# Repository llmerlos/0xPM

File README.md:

# PICCTRL - 0xPM
## 3x6 + 4 Split Ortholinear Keyboard with on board MCU

## Characteristics:
* [FAK](https://github.com/semickolon/fak) powered
* CH552
* ESD, over-current, short-circuit, reverse polarity protection.
* [Acrylic case](https://github.com/llmerlos/OxPM/PCB/svgs).
* Reversible PCB
* MX and Choc V1 compatibility.

### Choc V1

### MX

### Keymap
Nickel files available [here](https://github.com/llmerlos/OxPM/firmware/).

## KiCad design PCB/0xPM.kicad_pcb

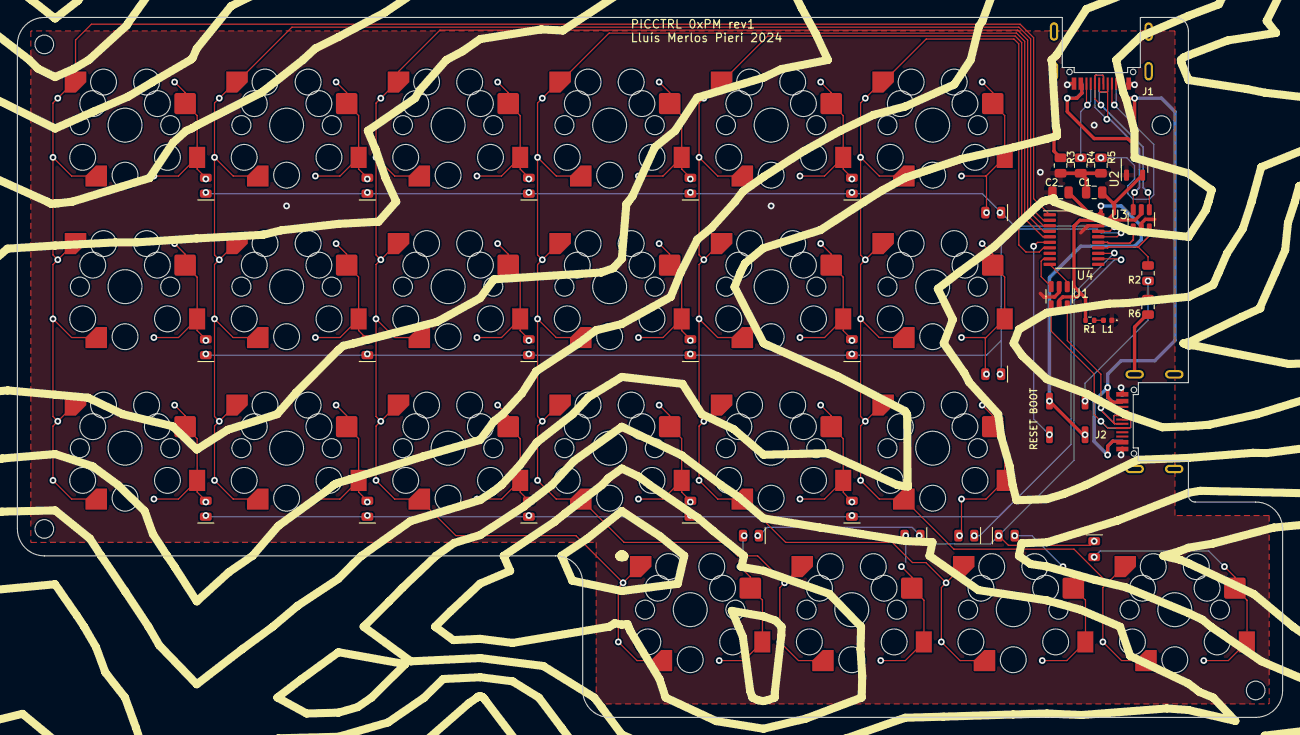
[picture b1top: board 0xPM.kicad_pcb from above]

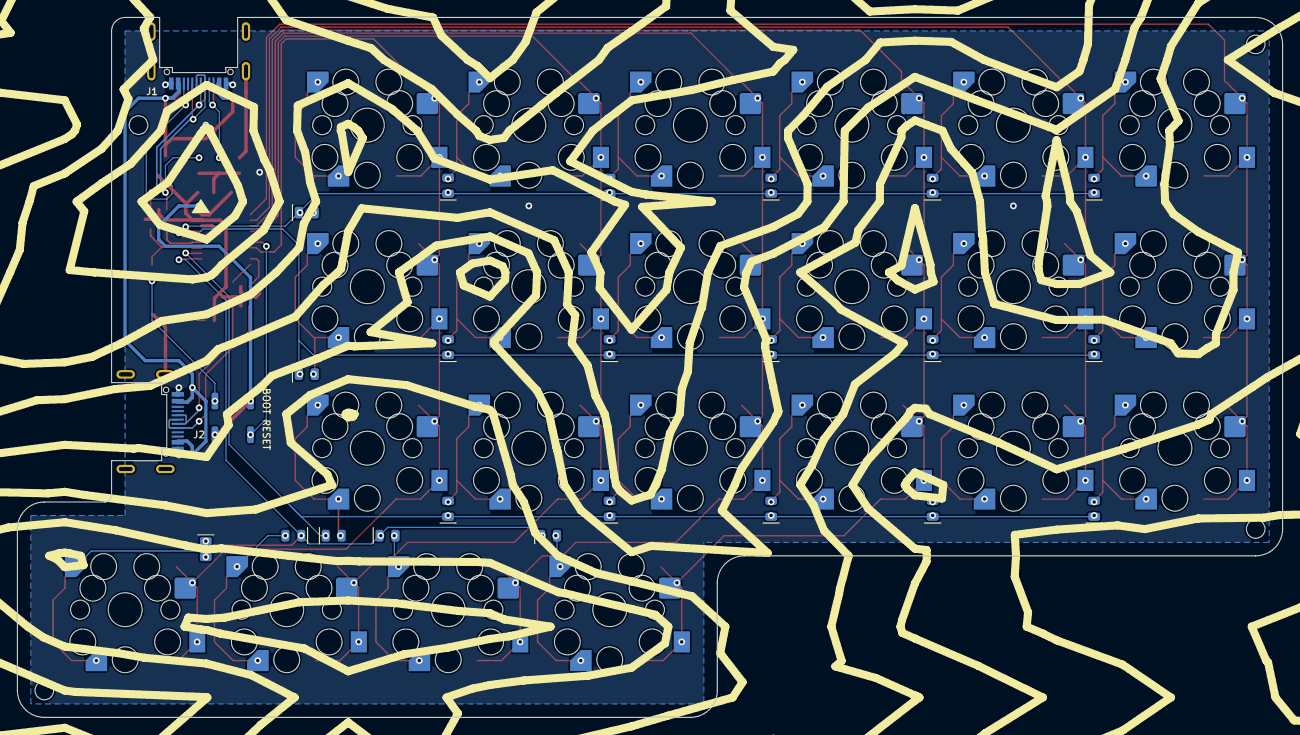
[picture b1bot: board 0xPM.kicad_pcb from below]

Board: 2 copper layers, 149.2 x 82.5 mm, 61 parts (22 on the bottom side), 51 nets.

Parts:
B1: BOOT; SW_Push_SPST_NO_Alps_SKRK
B2: RESET; SW_Push_SPST_NO_Alps_SKRK
C1, C2: 100nF; C_0805_2012Metric
D1, D2, D3, D4, D5, D6, D7, D8, D9, D10, D11, D12, D13, D14, D15, D16, D17, D18, D20, D21, D22, D23: D_Small_Filled; D_0805_2012Metric_Reversible
J1, J2: USB_C_Receptacle_USB2.0; TYPE-C-31-M-14_Reversible
L1: PWR/USR LED; LED_0402_1005Metric
R1: 1k; R_0402_1005Metric
R2, R4, R5: 5.1k; R_0805_2012Metric
R3, R6: 0; R_0805_2012Metric
SW1, SW2, SW3, SW4, SW5, SW6, SW7, SW8, SW9, SW10, SW11, SW12, SW13, SW14, SW15, SW16, SW17, SW18, SW20, SW21, SW22, SW23: SW_Push_45deg; SW_Hotswap_Kailh_Choc_MX_1.00u
U1, U3: USBLC6-2SC6; SOT-23-6
U2: CH213K; SOT-23-3
U4: CH552T; TSSOP-20_4.4x6.5mm_P0.65mm

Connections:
+3V3: B1.2, B2.1, C2.1, U4.20 (V33)
+5V: C1.1, R1.1, U1.5 (VBUS), U2.2 (VO-), U3.5 (VBUS), U4.19 (VCC)
COL1: SW1.1, SW7.1, SW13.1, U4.1 (P3.2)
COL2: SW2.1, SW8.1, SW14.1, U4.2 (P1.4)
COL3: SW3.1, SW9.1, SW15.1, SW20.1, U4.3 (P1.5)
COL4: SW4.1, SW10.1, SW16.1, SW21.1, U4.4 (P1.6)
COL5: SW5.1, SW11.1, SW17.1, SW22.1, U4.5 (P1.7)
COL6: SW6.1, SW12.1, SW18.1, SW23.1, U4.7 (P1.0)
D+: R2.1, U3.3 (I/O2), U4.14 (P3.6)
D-: U3.1 (I/O1), U4.15 (P3.7)
GND: C1.2, C2.2, J1.A1 (GND), J1.A12 (GND), J1.B1 (GND), J1.B12 (GND), J2.A1 (GND), J2.A12 (GND), J2.B1 (GND), J2.B12 (GND), L1.1 (K), R3.2, R4.2, R5.1, R6.2, U1.2 (GND), U2.1 (GND), U3.2 (GND), U4.18 (GND)
unnamed: B1.1, R2.2
unnamed: D1.2 (A), SW1.2
unnamed: D2.2 (A), SW2.2
unnamed: D3.2 (A), SW3.2
unnamed: D4.2 (A), SW4.2
unnamed: D5.2 (A), SW5.2
unnamed: D6.2 (A), SW6.2
unnamed: D7.2 (A), SW7.2
unnamed: D8.2 (A), SW8.2
unnamed: D9.2 (A), SW9.2
unnamed: D10.2 (A), SW10.2
unnamed: D11.2 (A), SW11.2
unnamed: D12.2 (A), SW12.2
unnamed: D13.2 (A), SW13.2
unnamed: D14.2 (A), SW14.2
unnamed: D15.2 (A), SW15.2
unnamed: D16.2 (A), SW16.2
unnamed: D17.2 (A), SW17.2
unnamed: D18.2 (A), SW18.2
unnamed: D20.2 (A), SW20.2
unnamed: D21.2 (A), SW21.2
unnamed: D22.2 (A), SW22.2
unnamed: D23.2 (A), SW23.2
unnamed: J1.A5 (CC1), R5.2
unnamed: J1.B5 (CC2), R4.1
unnamed: J1.S1 (SHIELD), R3.1
unnamed: J2.S1 (SHIELD), R6.1
unnamed: L1.2 (A), R1.2
P_D+: J1.A6 (D+), J1.B6 (D+), U3.4 (I/O2)
P_D-: J1.A7 (D-), J1.B7 (D-), U3.6 (I/O1)
P_RX: J2.A7 (D-), J2.B7 (D-), U1.6 (I/O1)
P_TX: J2.A6 (D+), J2.B6 (D+), U1.4 (I/O2)
ROW1: D1.1 (K), D2.1 (K), D3.1 (K), D4.1 (K), D5.1 (K), D6.1 (K), U4.17 (P1.2)
ROW2: D7.1 (K), D8.1 (K), D9.1 (K), D10.1 (K), D11.1 (K), D12.1 (K), U4.16 (P1.3)
ROW3: D13.1 (K), D14.1 (K), D15.1 (K), D16.1 (K), D17.1 (K), D18.1 (K), U4.13 (P3.5)
ROW4: D20.1 (K), D21.1 (K), D22.1 (K), D23.1 (K), U4.12 (P3.4)
RST: B2.2, U4.6 (RST)
RX: U1.1 (I/O1), U4.10 (P3.0)
TX: U1.3 (I/O2), U4.9 (P3.1)
VBUS: J1.A4 (VBUS), J1.A9 (VBUS), J1.B4 (VBUS), J1.B9 (VBUS), J2.A4 (VBUS), J2.A9 (VBUS), J2.B4 (VBUS), J2.B9 (VBUS), U2.3 (VI+)

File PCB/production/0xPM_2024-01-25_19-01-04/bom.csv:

Designator,Footprint,Quantity,Value,LCSC Part #
B1,SW_Push_SPST_NO_Alps_SKRK,1,BOOT,
B2,SW_Push_SPST_NO_Alps_SKRK,1,RESET,
"C1, C2",0805,2,100nF,
"D1, D10, D11, D12, D13, D14, D15, D16, D17, D18, D2, D20, D21, D22, D23, D3, D4, D5, D6, D7, D8, D9",0805,22,D_Small_Filled,
"J1, J2",TYPE-C-31-M-14_Reversible,2,USB_C_Receptacle_USB2.0,
L1,0402,1,PWR/USR LED,C130724
R1,0402,1,1k,C11702
"R2, R4, R5",0805,3,5.1k,
"R3, R6",0805,2,0,
"SW1, SW10, SW11, SW12, SW13, SW14, SW15, SW16, SW17, SW18, SW2, SW20, SW21, SW22, SW23, SW3, SW4, SW5, SW6, SW7, SW8, SW9",SW_Hotswap_Kailh_Choc_MX_1.00u,22,SW_Push_45deg,
"U1, U3",SOT-23-6,2,USBLC6-2SC6,
U2,SOT-23-3,1,CH213K,
U4,TSSOP-20_4.4x6.5mm_P0.65mm,1,CH552T,

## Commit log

2024-01-25 add license
2024-01-26 added pdf schematic
2024-02-20 pretty repo
2024-03-12 updated layout
